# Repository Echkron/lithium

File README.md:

# lithium
ortholinear low profile split keyboard
unfinished, untested and incomplete. use at your own risk.

there are (will be) 2 sets of pcbs available, standard and segmented

standard uses a single pcb for each side of the split

segmented uses a motherboard for the mcu and 2 daughterboards for the keys per side of the split, in order to fit the purchased pcbs into 10x10 cm for seeed studio's extremely cheap fusionpcb service. the daughterboards are connected to the motherboard via ribbion connectors. segmented boards are lettered A and C, with the mcu/motherboard being A (daughterboard B is on the same pcb/gerber), and daugheterboard C.

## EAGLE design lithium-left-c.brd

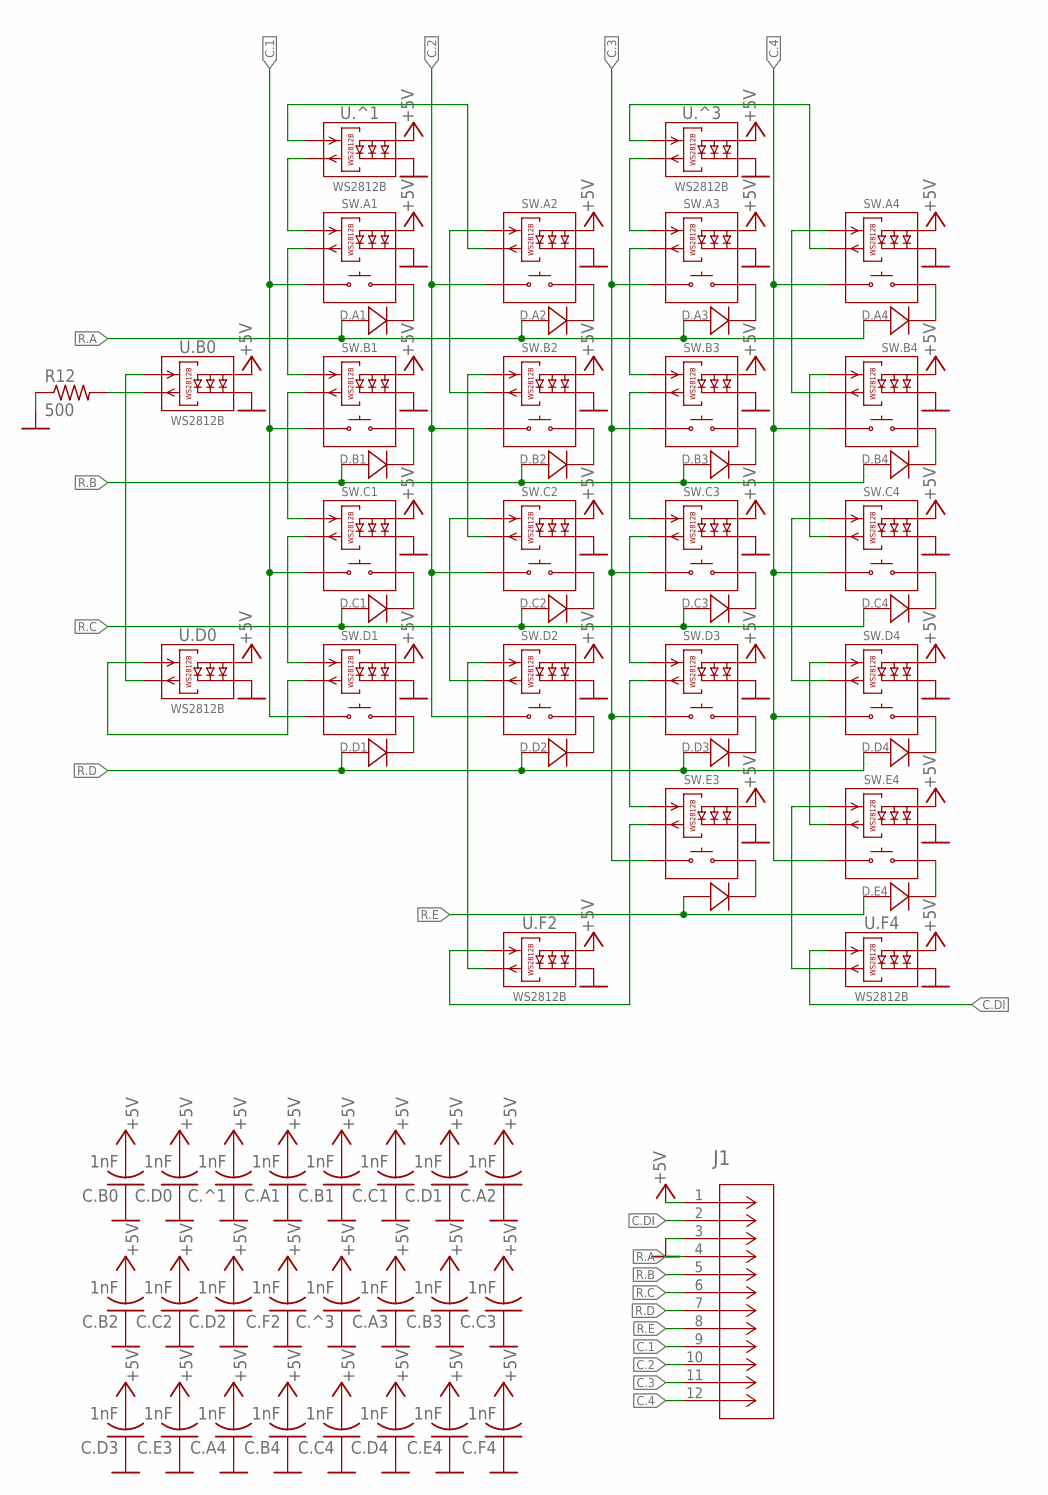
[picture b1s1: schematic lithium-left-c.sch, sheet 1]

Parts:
C.A1, C.A2, C.A3, C.A4, C.B0, C.B1, C.B2, C.B3, C.B4, C.C1, C.C2, C.C3, C.C4, C.D0, C.D1, C.D2, C.D3, C.D4, C.E3, C.E4, C.F2, C.F4, C.^1, C.^3: 1nF; C0805
D.A1, D.A2, D.A3, D.A4, D.B1, D.B2, D.B3, D.B4, D.C1, D.C2, D.C3, D.C4, D.D1, D.D2, D.D3, D.D4, D.E3, D.E4: 1N4148W; CR_48W-E3-08_VIS
J1: FFC2B28-12-G; CONN_FFC2B28-12-G_GCT
R12: 500; R0805
SW.A1, SW.A2, SW.A3, SW.A4, SW.B1, SW.B2, SW.B3, SW.B4, SW.C1, SW.C2, SW.C3, SW.C4, SW.D1, SW.D2, SW.D3, SW.D4, SW.E3, SW.E4: PG1350_LEDSD; PG1350_SD/SK68
U.B0, U.D0, U.F2, U.F4, U.^1, U.^3: WS2812B; SK68-R

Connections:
+5V: C.A1.2, C.A2.2, C.A3.2, C.A4.2, C.B0.2, C.B1.2, C.B2.2, C.B3.2, C.B4.2, C.C1.2, C.C2.2, C.C3.2, C.C4.2, C.D0.2, C.D1.2, C.D2.2, C.D3.2, C.D4.2, C.E3.2, C.E4.2, C.F2.2, C.F4.2, C.^1.2, C.^3.2, J1.1, SW.A1.1-VDD (VDD), SW.A2.1-VDD (VDD), SW.A3.1-VDD (VDD), SW.A4.1-VDD (VDD), SW.B1.1-VDD (VDD), SW.B2.1-VDD (VDD), SW.B3.1-VDD (VDD), SW.B4.1-VDD (VDD), SW.C1.1-VDD (VDD), SW.C2.1-VDD (VDD), SW.C3.1-VDD (VDD), SW.C4.1-VDD (VDD), SW.D1.1-VDD (VDD), SW.D2.1-VDD (VDD), SW.D3.1-VDD (VDD), SW.D4.1-VDD (VDD), SW.E3.1-VDD (VDD), SW.E4.1-VDD (VDD), U.B0.1-VDD (VDD), U.D0.1-VDD (VDD), U.F2.1-VDD (VDD), U.F4.1-VDD (VDD), U.^1.1-VDD (VDD), U.^3.1-VDD (VDD)
C.1: J1.9, SW.A1.1, SW.B1.1, SW.C1.1, SW.D1.1
C.2: J1.10, SW.A2.1, SW.B2.1, SW.C2.1, SW.D2.1
C.3: J1.11, SW.A3.1, SW.B3.1, SW.C3.1, SW.D3.1, SW.E3.1
C.4: J1.12, SW.A4.1, SW.B4.1, SW.C4.1, SW.D4.1, SW.E4.1
C.DI: J1.2, U.F4.4-DIN (DI)
GND: C.A1.1, C.A2.1, C.A3.1, C.A4.1, C.B0.1, C.B1.1, C.B2.1, C.B3.1, C.B4.1, C.C1.1, C.C2.1, C.C3.1, C.C4.1, C.D0.1, C.D1.1, C.D2.1, C.D3.1, C.D4.1, C.E3.1, C.E4.1, C.F2.1, C.F4.1, C.^1.1, C.^3.1, J1.3, R12.1, SW.A1.3-GND (GND), SW.A2.3-GND (GND), SW.A3.3-GND (GND), SW.A4.3-GND (GND), SW.B1.3-GND (GND), SW.B2.3-GND (GND), SW.B3.3-GND (GND), SW.B4.3-GND (GND), SW.C1.3-GND (GND), SW.C2.3-GND (GND), SW.C3.3-GND (GND), SW.C4.3-GND (GND), SW.D1.3-GND (GND), SW.D2.3-GND (GND), SW.D3.3-GND (GND), SW.D4.3-GND (GND), SW.E3.3-GND (GND), SW.E4.3-GND (GND), U.B0.3-GND (GND), U.D0.3-GND (GND), U.F2.3-GND (GND), U.F4.3-GND (GND), U.^1.3-GND (GND), U.^3.3-GND (GND)
unnamed: D.A1.1, SW.A1.2
unnamed: D.B1.1, SW.B1.2
unnamed: D.C1.1, SW.C1.2
unnamed: D.B2.1, SW.B2.2
unnamed: D.D1.1, SW.D1.2
unnamed: D.A2.1, SW.A2.2
unnamed: D.C2.1, SW.C2.2
unnamed: D.D2.1, SW.D2.2
unnamed: D.B3.1, SW.B3.2
unnamed: D.C3.1, SW.C3.2
unnamed: D.A3.1, SW.A3.2
unnamed: D.D3.1, SW.D3.2
unnamed: D.B4.1, SW.B4.2
unnamed: D.E3.1, SW.E3.2
unnamed: D.C4.1, SW.C4.2
unnamed: D.A4.1, SW.A4.2
unnamed: D.D4.1, SW.D4.2
unnamed: D.E4.1, SW.E4.2
unnamed: SW.A2.2-DOUT (DO), U.^1.4-DIN (DI)
unnamed: SW.D1.2-DOUT (DO), U.D0.4-DIN (DI)
unnamed: SW.A2.4-DIN (DI), SW.B2.2-DOUT (DO)
unnamed: SW.B2.4-DIN (DI), SW.C2.2-DOUT (DO)
unnamed: SW.A1.4-DIN (DI), U.^1.2-DOUT (DO)
unnamed: SW.A1.2-DOUT (DO), SW.B1.4-DIN (DI)
unnamed: SW.B1.2-DOUT (DO), SW.C1.4-DIN (DI)
unnamed: SW.C1.2-DOUT (DO), SW.D1.4-DIN (DI)
unnamed: R12.2, U.B0.2-DOUT (DO)
unnamed: SW.D3.2-DOUT (DO), SW.E3.4-DIN (DI)
unnamed: SW.C3.2-DOUT (DO), SW.D3.4-DIN (DI)
unnamed: SW.B3.2-DOUT (DO), SW.C3.4-DIN (DI)
unnamed: SW.A3.2-DOUT (DO), SW.B3.4-DIN (DI)
unnamed: SW.A3.4-DIN (DI), U.^3.2-DOUT (DO)
unnamed: SW.E3.2-DOUT (DO), U.F2.4-DIN (DI)
unnamed: U.B0.4-DIN (DI), U.D0.2-DOUT (DO)
unnamed: SW.C4.4-DIN (DI), SW.D4.2-DOUT (DO)
unnamed: SW.B4.4-DIN (DI), SW.C4.2-DOUT (DO)
unnamed: SW.A4.4-DIN (DI), SW.B4.2-DOUT (DO)
unnamed: SW.C2.4-DIN (DI), SW.D2.2-DOUT (DO)
unnamed: SW.A4.2-DOUT (DO), U.^3.4-DIN (DI)
unnamed: SW.D4.4-DIN (DI), SW.E4.2-DOUT (DO)
unnamed: SW.D2.4-DIN (DI), U.F2.2-DOUT (DO)
unnamed: SW.E4.4-DIN (DI), U.F4.2-DOUT (DO)
R.A: D.A1.2, D.A2.2, D.A3.2, D.A4.2, J1.4
R.B: D.B1.2, D.B2.2, D.B3.2, D.B4.2, J1.5
R.C: D.C1.2, D.C2.2, D.C3.2, D.C4.2, J1.6
R.D: D.D1.2, D.D2.2, D.D3.2, D.D4.2, J1.7
R.E: D.E3.2, D.E4.2, J1.8

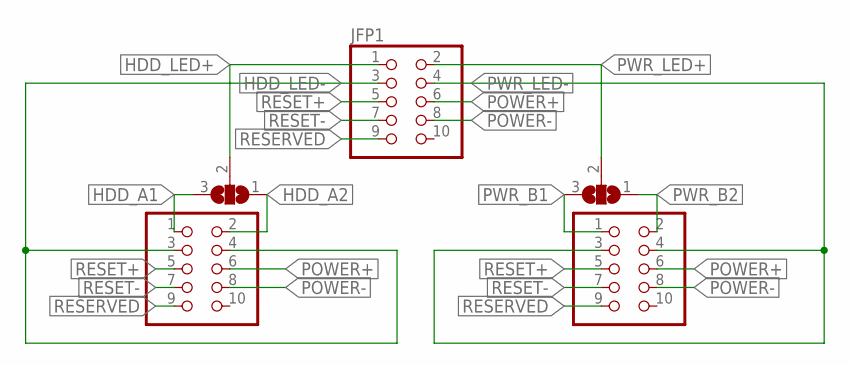
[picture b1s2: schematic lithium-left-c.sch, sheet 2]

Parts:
HDD_LED: PINHD-2X5; 2X05
JFP1: PINHD-2X5; 2X05
J_HDD: SJ2W; SJ_2
J_PWR: SJ2W; SJ_2
PWR_LED: PINHD-2X5; 2X05

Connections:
HDD_A1: HDD_LED.1, J_HDD.3
HDD_A2: HDD_LED.2, J_HDD.1
HDD_LED+: JFP1.1, J_HDD.2
HDD_LED-: HDD_LED.3, HDD_LED.4, JFP1.3
POWER+: HDD_LED.6, JFP1.6, PWR_LED.6
POWER-: HDD_LED.8, JFP1.8, PWR_LED.8
PWR_B1: J_PWR.3, PWR_LED.1
PWR_B2: J_PWR.1, PWR_LED.2
PWR_LED+: JFP1.2, J_PWR.2
PWR_LED-: JFP1.4, PWR_LED.3, PWR_LED.4
RESERVED: HDD_LED.9, JFP1.9, PWR_LED.9
RESET+: HDD_LED.5, JFP1.5, PWR_LED.5
RESET-: HDD_LED.7, JFP1.7, PWR_LED.7

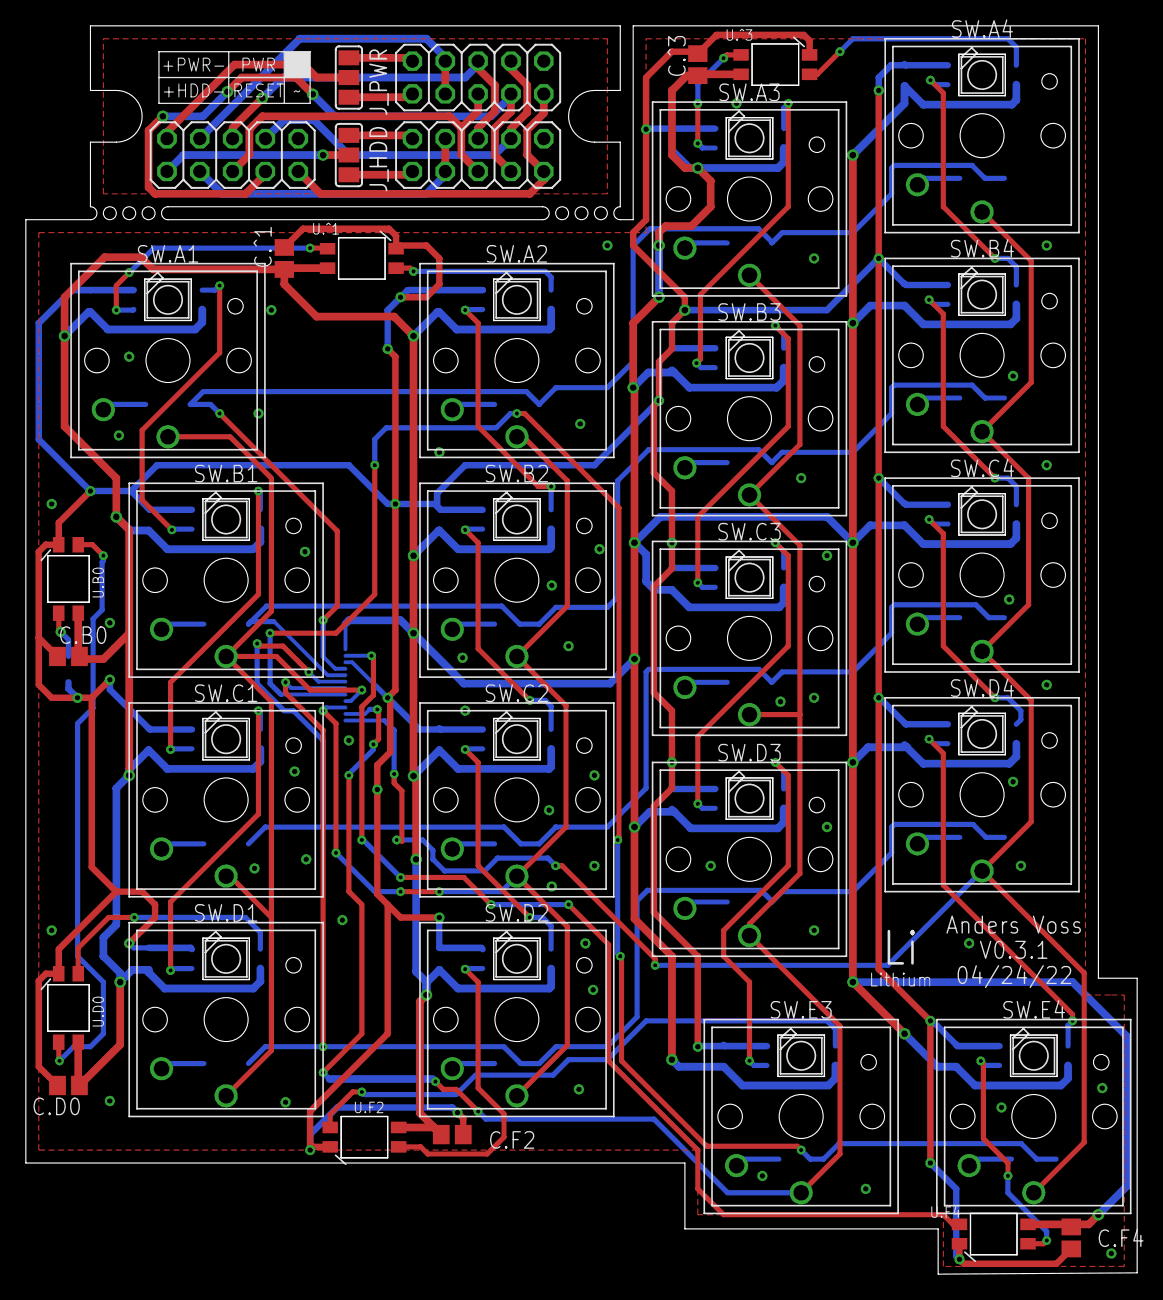
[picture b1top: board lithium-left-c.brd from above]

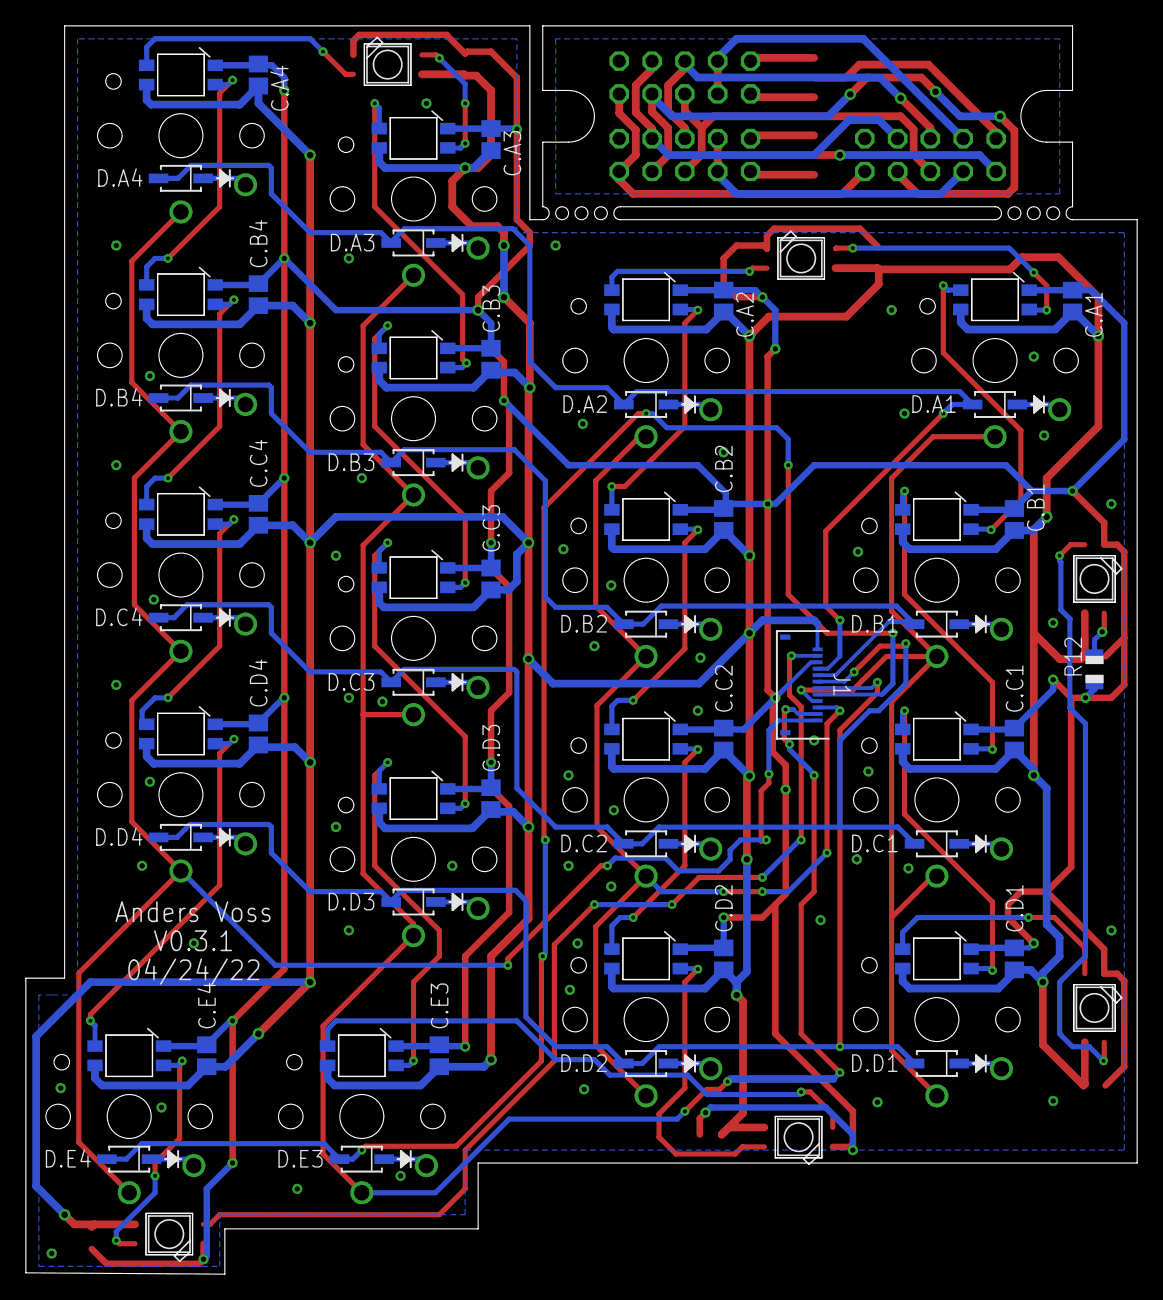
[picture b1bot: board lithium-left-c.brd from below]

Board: 2 copper layers, 85.9 x 96.5 mm, 73 parts (44 on the bottom side), 67 nets.

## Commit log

2022-04-25 Add initial daughterboard schematic and board
    daughterboard c for left hand
